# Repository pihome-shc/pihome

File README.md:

<p align="center">
    
<br/>
</p>

# PiHome - Smart Heating Control

PiHome – Smart Heating Control is home automation system or you can say central heating control systems that runs on credit card size single board computer Raspberry Pi. You can control your home heating from your smartphone, laptop or tablet, PiHome is a wireless boiler control which mean you don’t need to run cables from pihome controller to your boiler or to your heating zone valve or to any temperature sensors in any heating zone.PiHome is active heating control of your multi zoned heating, hot water including electrical immersion with unlimited schedules, boost and night climate suites your needs.

[Step by Step Instructions](http://www.pihome.eu/how-to-install/ "PiHome - Step by Step Instructions")

<p style="color:red;">Before we deep dive into this project something very important: PiHome comes with ABSOLUTELY NO WARRANTY, to the extent permitted by applicable law. DO NOT MAKE ANY CHANGES TO YOUR HEATING SYSTEM UNTIL UNLESS YOU KNOW WHAT YOU ARE DOING, contents provided here are for information and education purpose only, I take no responsibility for any loss or damage to you or your property.”</p3>

###If you want to download SD card image for Raspberry Pi please visit http://www.pihome.eu 

## Smart Heating Control – Features:
* Support Serial Gateway
* Support Ethernet and WiFi Gateway
* Unlimited schedule 
* Boiler and heating zone usage graphs
* Boost control for each Zone
* Override for each Zone
* Night climate
* Away

## Planned features
A real documentation (currently there's none, but the code is self explanatory and commented as well )

Follow Instructions on [PiHome](http://www.pihome.eu "PiHome - Smart Heating Control") if you have any question drop me comments and i will do my best to reply as soon as humanely possible. 

## Requirements
Basic knowledge of command line with following main components for pihome to function. 
* Apache Web Server
* PHP 7.x
* MySQL/MariaDB 

## How To Install 
sudo apt-get install git
sudo git clone https://github.com/pihome-shc/pihome "/var/www"
For more detailed instructiosn vist [PiHome](http://www.pihome.eu "PiHome - Smart Heating Control") website 

## Secial Thanks to

* [SB Admin 2 Template](http://startbootstrap.com/template-overviews/sb-admin-2 "SB Admin 2 Template ")
* [Pretty Checkbox](http://www.cssscript.com/pretty-checkbox-radio-inputs-bootstrap-awesome-bootstrap-checkbox-css "Pretty Checkbox ")
* [Font-Awesome](https://fortawesome.github.io/Font-Awesome "Font-Awesome")
* [Ionicons](http://ionicons.com "Ionicons ")
* [Box Shadow CSS](http://www.cssmatic.com/box-shadow "Box Shadow CSS")
* [AnimateCSS](https://daneden.github.io/animate.css "Animate.css ")
* [MySensors](https://www.mysensors.org "MySensors")
* [RaspberryPi Home Automation](http://pihome.harkemedia.de "RaspberryPi Home Automation")
* [All Others if forget them...](http://www.pihome.eu "All Others if forget them...")

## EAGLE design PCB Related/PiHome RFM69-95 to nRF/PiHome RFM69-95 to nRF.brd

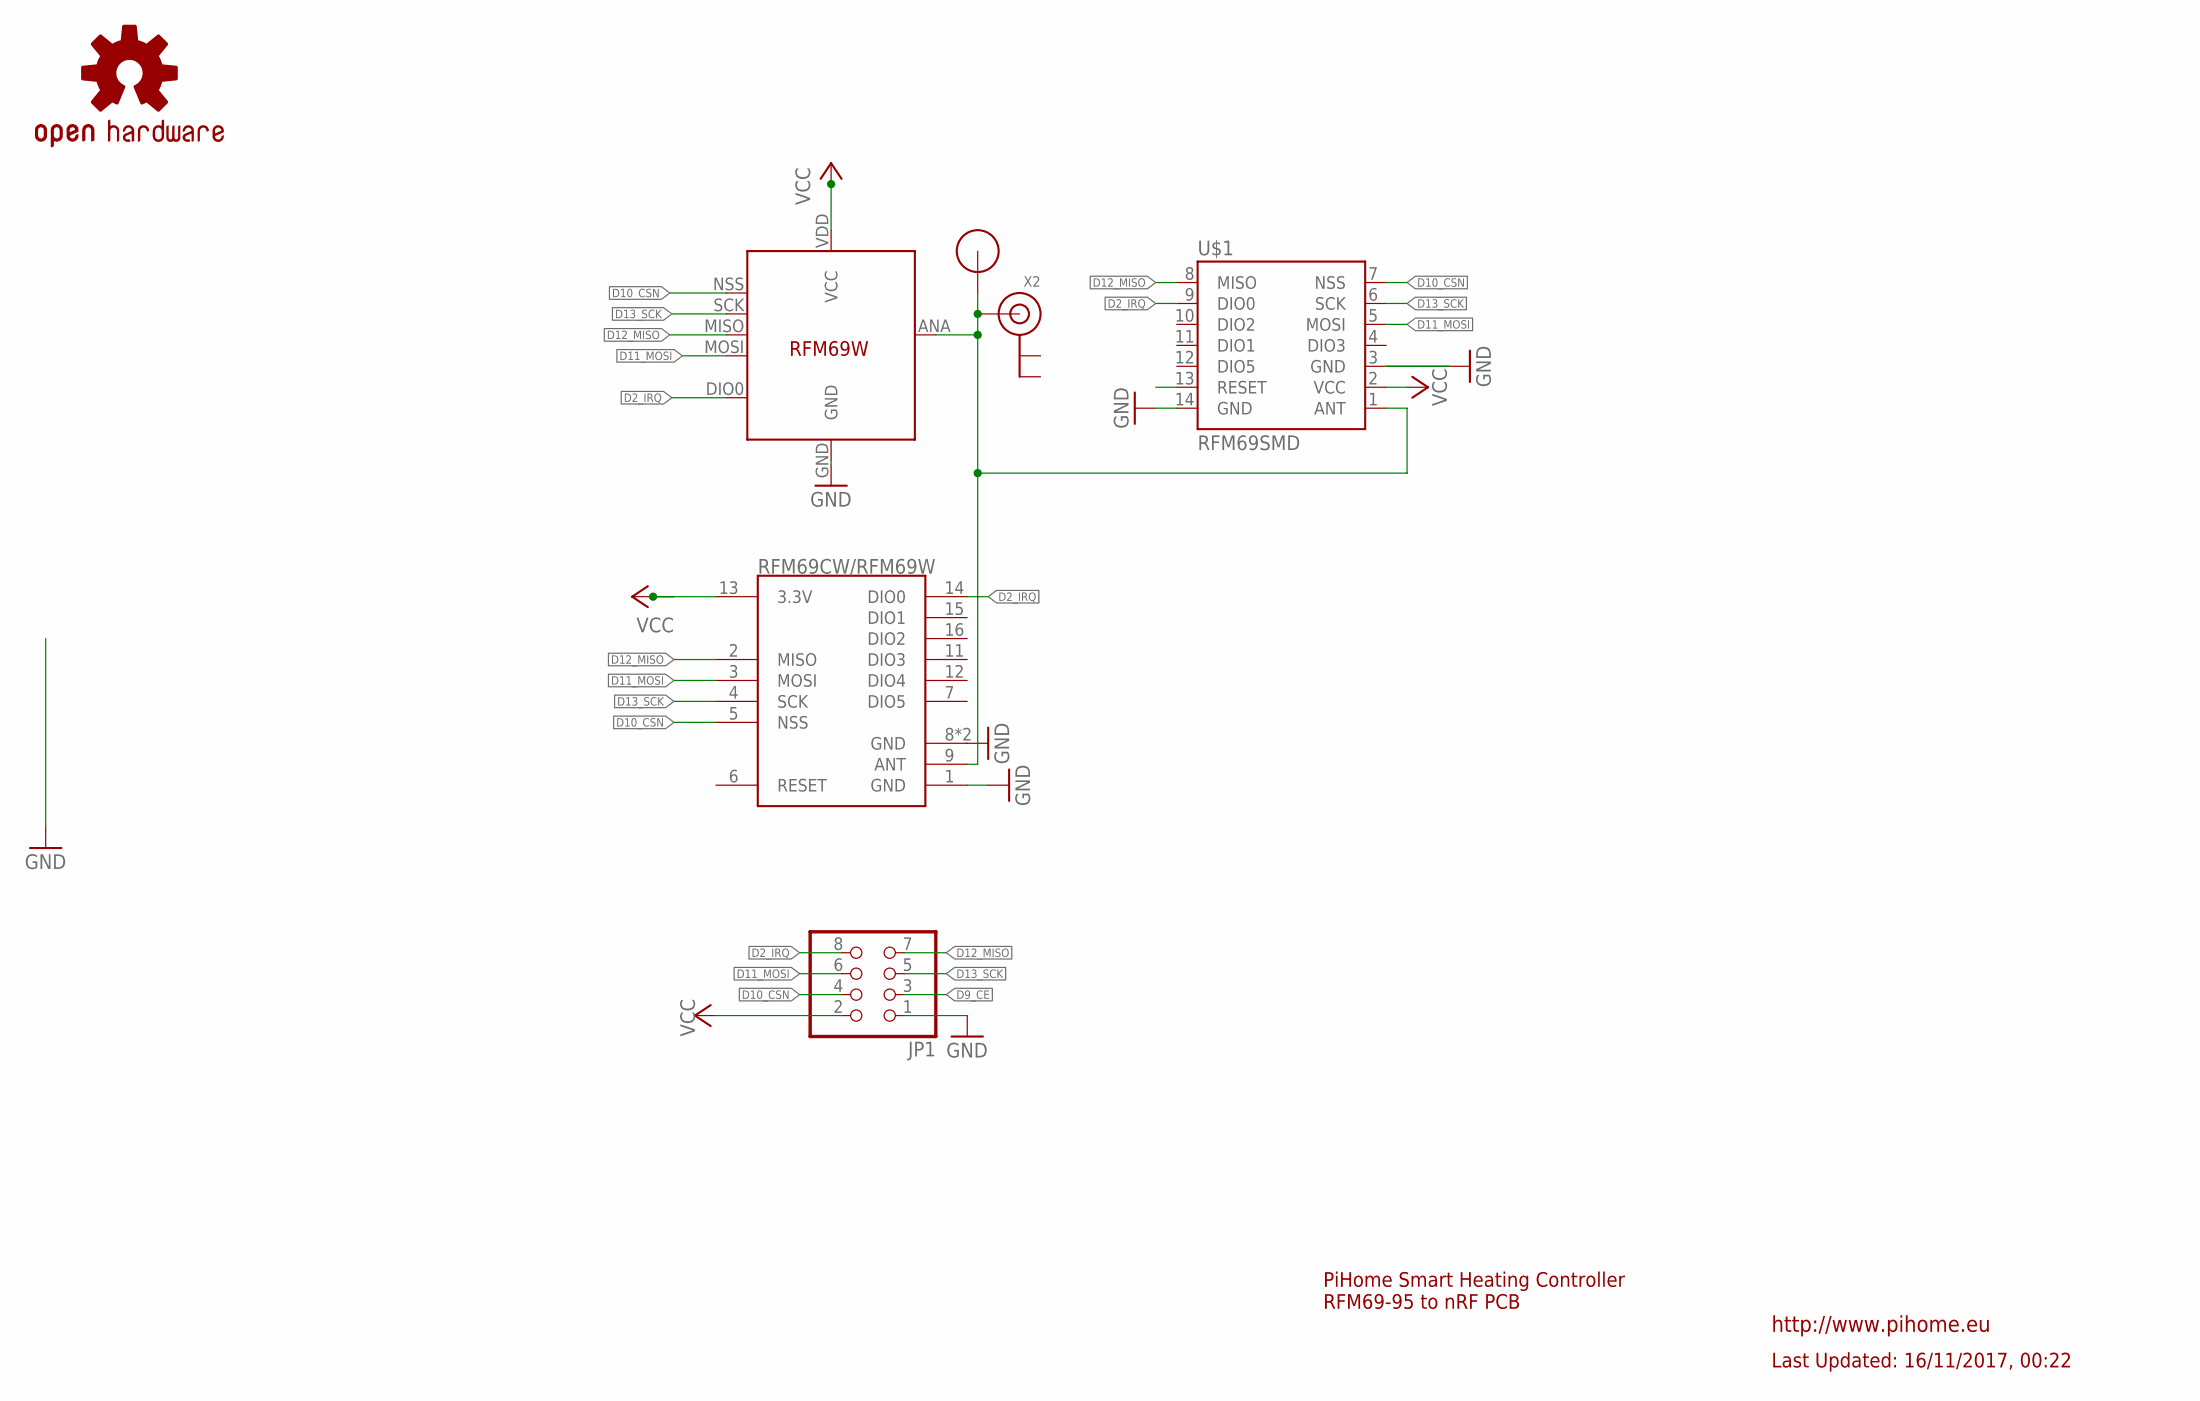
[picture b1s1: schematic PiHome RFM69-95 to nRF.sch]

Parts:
JP1: PINHD-2X4; 2X04
LOGO2: OSHW-LOGOS; OSHW-LOGO-S
RFM69CW/RFM69W: RFM69HCW; RFM69HCW-XXXS2
RFM69W-433MHZ: RFM69; RFM69W-MINPADS
U$1: RFM69SMD; RFM69
U$6: RFM12B_ANTENNA; RFM12B-ANTENNA
X2: ANTENNA_U.FL; U.FL

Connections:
D2_IRQ: JP1.8, RFM69CW/RFM69W.14 (DIO0), RFM69W-433MHZ.DIO0, U$1.9 (DIO0)
D9_CE: JP1.3
D10_CSN: JP1.4, RFM69CW/RFM69W.5 (NSS), RFM69W-433MHZ.NSS (SEL), U$1.7 (NSS)
D11_MOSI: JP1.6, RFM69CW/RFM69W.3 (MOSI), RFM69W-433MHZ.MOSI, U$1.5 (MOSI)
D12_MISO: JP1.7, RFM69CW/RFM69W.2 (MISO), RFM69W-433MHZ.MISO, U$1.8 (MISO)
D13_SCK: JP1.5, RFM69CW/RFM69W.4 (SCK), RFM69W-433MHZ.SCK, U$1.6 (SCK)
GND: JP1.1, RFM69CW/RFM69W.1 (GND), RFM69CW/RFM69W.8 (GND), RFM69CW/RFM69W.10 (GND), RFM69W-433MHZ.GND, U$1.3 (GND), U$1.14 (GND)
unnamed: RFM69CW/RFM69W.9 (ANT), RFM69W-433MHZ.ANA (ANT), U$1.1 (ANT), U$6.P$1, X2.3 (SIGNAL)
VCC: JP1.2, RFM69CW/RFM69W.13 (3.3V), RFM69W-433MHZ.VDD (VCC), U$1.2 (VCC)

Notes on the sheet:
PiHome Smart Heating Controller RFM69-95 to nRF PCB
Last Updated: 16/11/2017, 00:22
http://www.pihome.eu

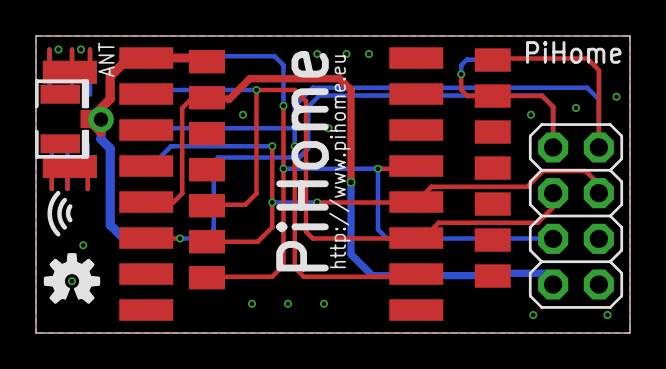
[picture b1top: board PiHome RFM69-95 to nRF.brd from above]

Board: 2 copper layers, 33.0 x 16.5 mm, 7 parts (1 on the bottom side), 8 nets.

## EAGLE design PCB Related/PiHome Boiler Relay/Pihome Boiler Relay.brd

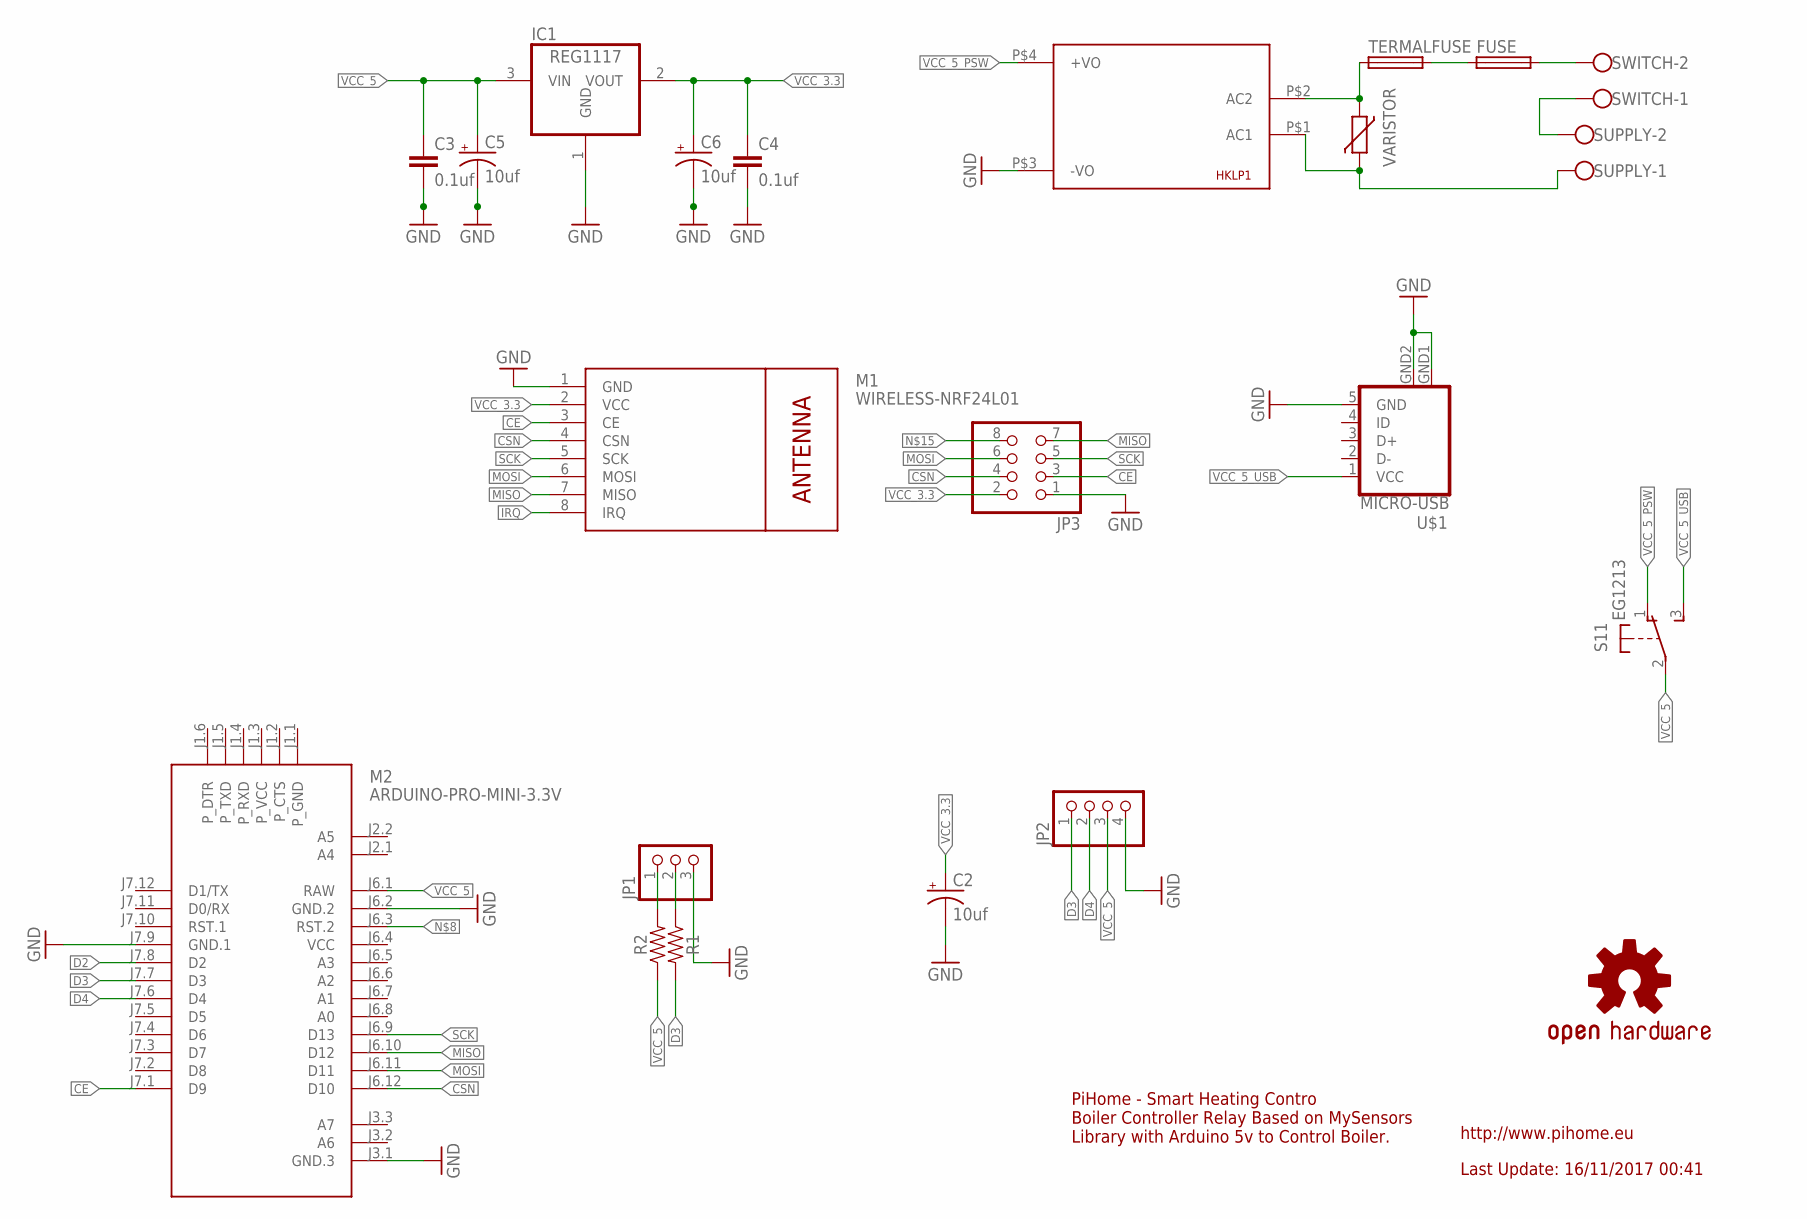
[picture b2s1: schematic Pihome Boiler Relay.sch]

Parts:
C2, C5, C6: 10uf; CPOL-RADIAL-10UF-25V-KIT
C3, C4: 0.1uf; CAP-PTH-SMALL-KIT
FUSE: TE5
HKLP1: HKLPM01
IC1: REG1117; SOT223
JP1: PINHD-1X3; 1X03
JP2: PINHD-1X4; 1X04
JP3: PINHD-2X4; 2X04
LOGO1: OSHW-LOGOL; OSHW-LOGO-L
M1: WIRELESS-NRF24L01
M2: ARDUINO-PRO-MINI-3.3V; ARDUINO-PRO-MINI
R1, R2: AXIAL-0.3
S1: EG1213
SUPPLY: W237-102
SWITCH: W237-102
TERMALFUSE: TE5
U$1: MICRO-USB
VARISTOR: VARISTOR-7,5; R-7,5

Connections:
CE: JP3.3, M1.3 (CE), M2.J7.1 (D9)
CSN: JP3.4, M1.4 (CSN), M2.J6.12 (D10)
D2: M2.J7.8 (D2)
D3: JP2.1, M2.J7.7 (D3), R1.P$2 (2)
D4: JP2.2, M2.J7.6 (D4)
GND: C2.2 (-), HKLP1.P$3 (-VO), JP1.3, JP2.4, JP3.1, M1.1 (GND), M2.J3.1 (GND.3), M2.J6.2 (GND.2), M2.J7.9 (GND.1), U$1.5 (GND), U$1.GND1 (GND), U$1.GND2 (GND)
GND-: C3.2, C4.2, C5.2 (-), C6.2 (-), IC1.1 (GND)
IRQ: M1.8 (IRQ)
MISO: JP3.7, M1.7 (MISO), M2.J6.10 (D12)
MOSI: JP3.6, M1.6 (MOSI), M2.J6.11 (D11)
unnamed: SUPPLY.2, SWITCH.1
unnamed: FUSE.1, TERMALFUSE.2
unnamed: HKLP1.P$2 (AC2), TERMALFUSE.1, VARISTOR.1
unnamed: HKLP1.P$1 (AC1), SUPPLY.1, VARISTOR.2
unnamed: JP1.2, R1.P$1 (1)
unnamed: JP1.1, R2.P$2 (2)
unnamed: FUSE.2, SWITCH.2
SCK: JP3.5, M1.5 (SCK), M2.J6.9 (D13)
VCC: M2.J6.4 (VCC)
VCC_3.3: C2.1 (+), C4.1, C6.1 (+), IC1.2 (VOUT), JP3.2, M1.2 (VCC)
VCC_5: C3.1, C5.1 (+), IC1.3 (VIN), JP2.3, M2.J6.1 (RAW), R2.P$1 (1), S1.2
VCC_5_PSW: HKLP1.P$4 (+VO), S1.1 (O)
VCC_5_USB: S1.3 (S), U$1.1 (VCC)

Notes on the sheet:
Last Update: 16/11/2017 00:41
http://www.pihome.eu
PiHome - Smart Heating Contro Boiler Controller Relay Based on MySensors Library with Arduino 5v to Control Boiler.

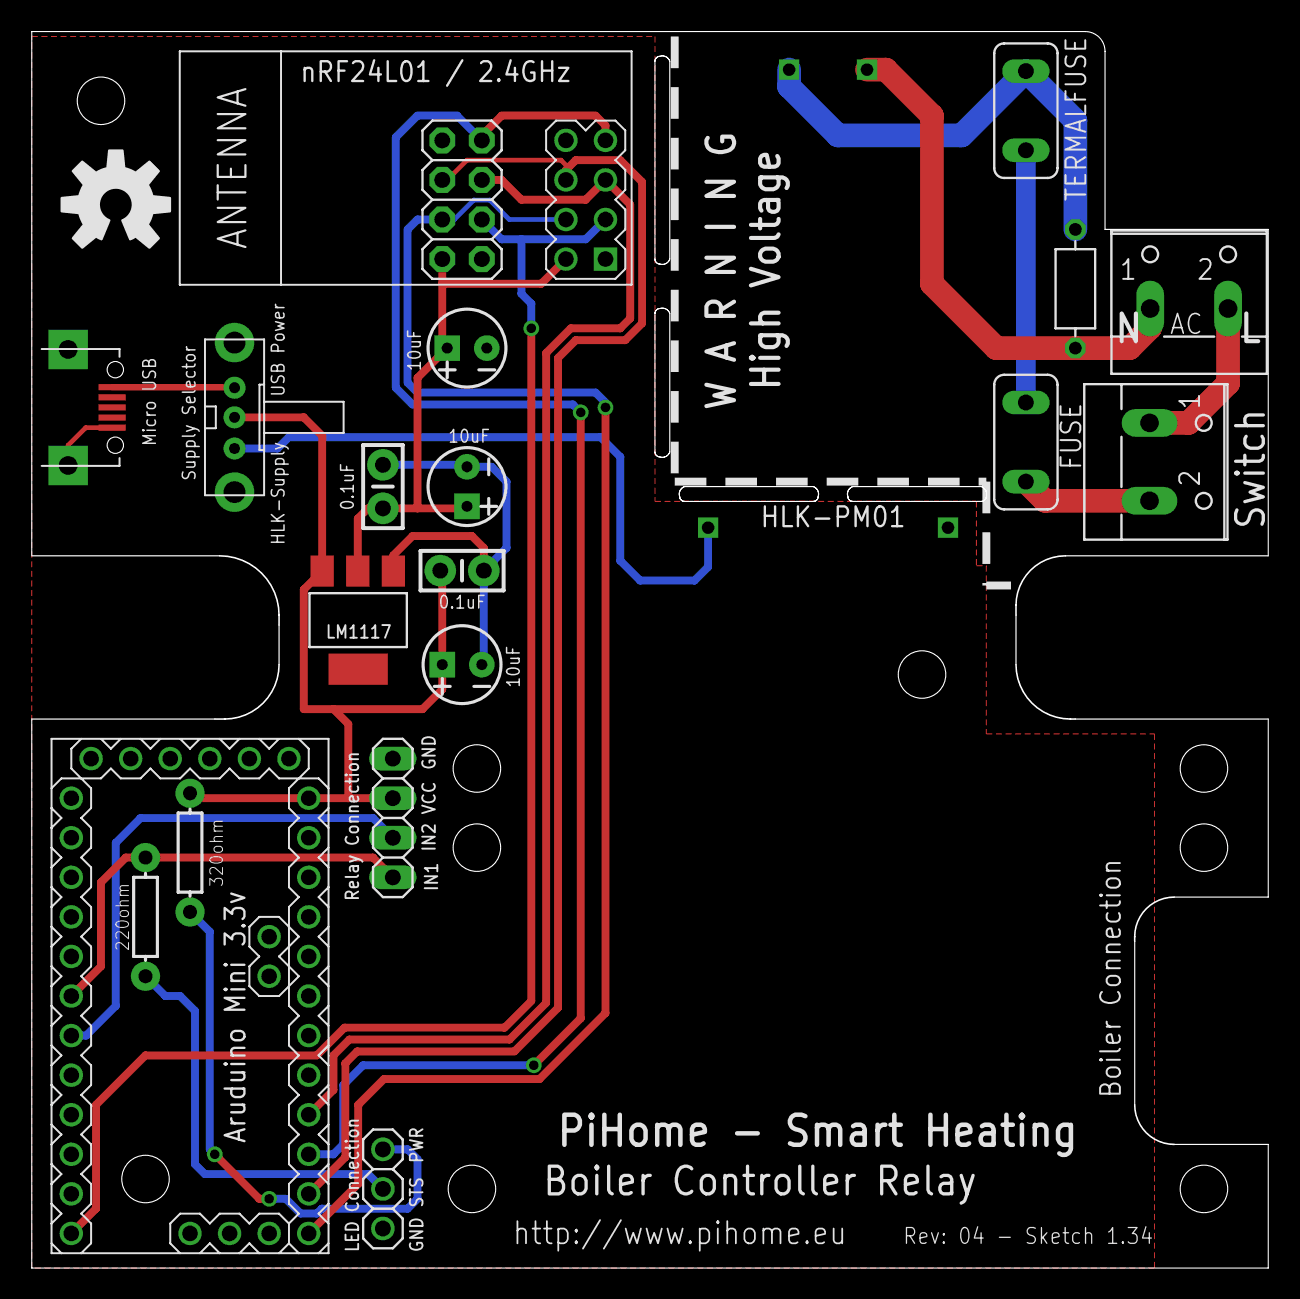
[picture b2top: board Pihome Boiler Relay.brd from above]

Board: 2 copper layers, 79.4 x 79.4 mm, 22 parts (0 on the bottom side), 20 nets.

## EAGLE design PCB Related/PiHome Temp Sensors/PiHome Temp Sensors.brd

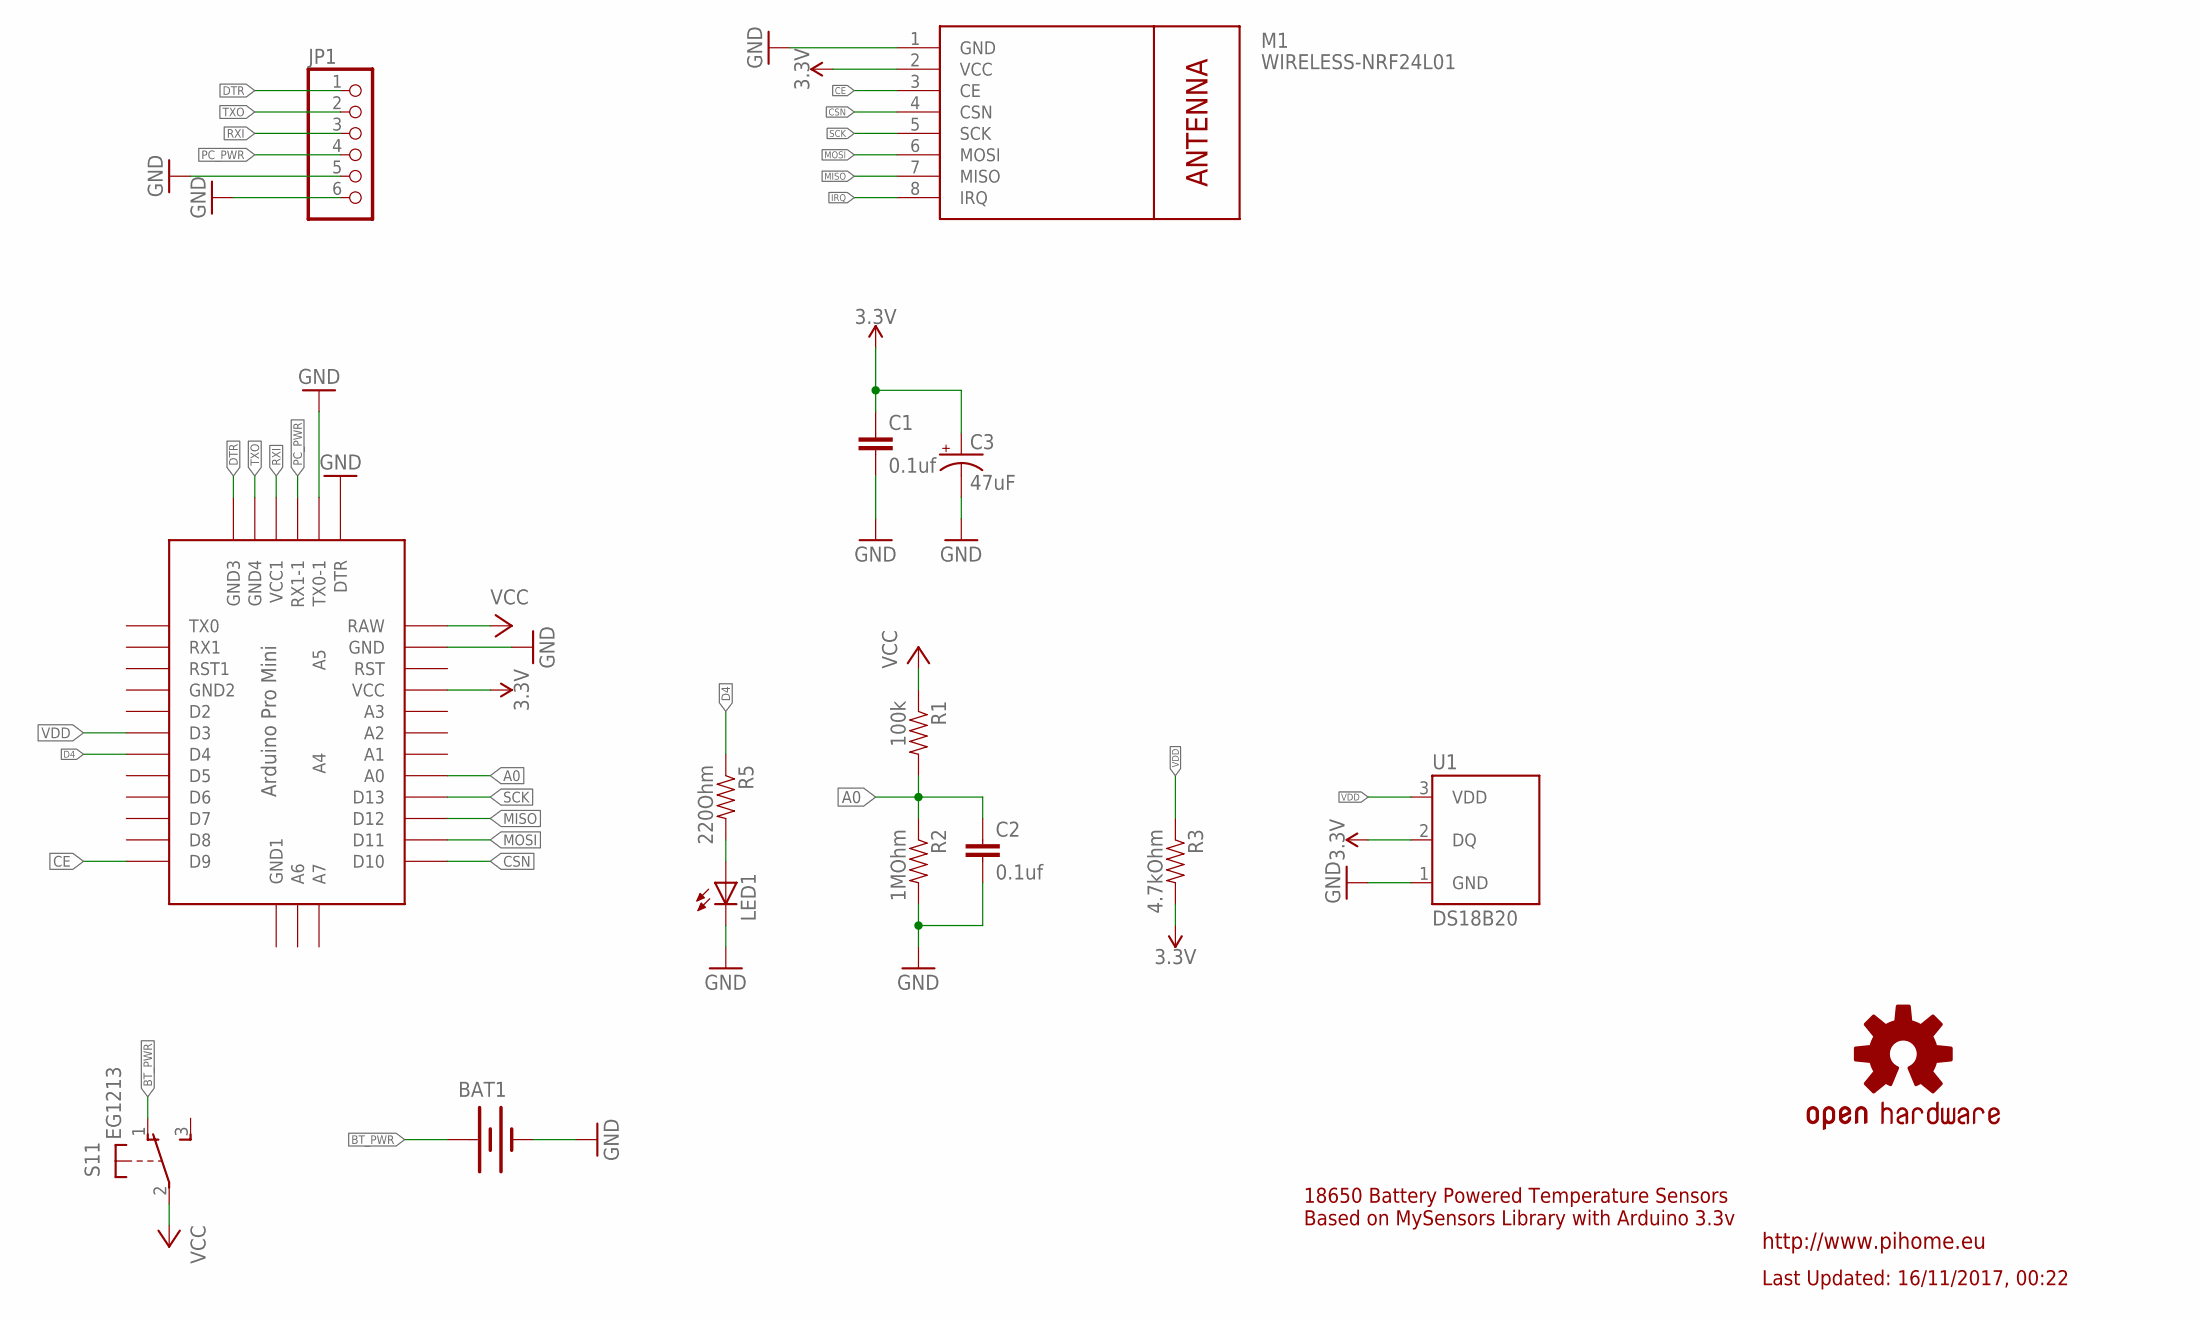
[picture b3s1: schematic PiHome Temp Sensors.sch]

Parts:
BAT1: BATTERY18650; BATTERY_18650-HOLDER
C1, C2: 0.1uf; CAP-PTH-SMALL-KIT
C3: 47uF; CPOL-RADIAL-10UF-25V-KIT
JP1: PINHD-1X6; 1X06
LED1: LED3MM
LOGO1: OSHW-LOGOL; OSHW-LOGO-L
M1: WIRELESS-NRF24L01
R1: 100k; AXIAL-0.3
R2: 1MOhm; AXIAL-0.3
R3: 4.7kOhm; AXIAL-0.3
R5: 220Ohm; AXIAL-0.3
S1: EG1213
U1: DS18B20; TO-92-AMMO
U$1: ABK-PRO-MINI

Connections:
3.3V: C1.1, C3.1 (+), M1.2 (VCC), R3.P$2 (2), U1.2 (DQ), U$1.VCC
A0: C2.1, R1.P$2 (2), R2.P$1 (1), U$1.A0
BT_PWR: BAT1.PWR@1 (+), S1.1 (O)
CE: M1.3 (CE), U$1.D9
CSN: M1.4 (CSN), U$1.D10
D4: R5.P$1 (1), U$1.D4
DTR: JP1.1, U$1.GND2 (GND3)
GND: BAT1.GND@1 (-), C1.2, C2.2, C3.2 (-), JP1.5, JP1.6, LED1.K (C), M1.1 (GND), R2.P$2 (2), U1.1 (GND), U$1.DTR, U$1.GND, U$1.TX0-1
IRQ: M1.8 (IRQ)
MISO: M1.7 (MISO), U$1.D12
MOSI: M1.6 (MOSI), U$1.D11
unnamed: LED1.A, R5.P$2 (2)
PC_PWR: JP1.4, U$1.RX1-1
RXI: JP1.3, U$1.VCC1
SCK: M1.5 (SCK), U$1.D13
TXO: JP1.2, U$1.GND3 (GND4)
VCC: R1.P$1 (1), S1.2, U$1.RAW
VDD: R3.P$1 (1), U1.3 (VDD), U$1.D3

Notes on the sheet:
18650 Battery Powered Temperature Sensors Based on MySensors Library with Arduino 3.3v
Last Updated: 16/11/2017, 00:22
http://www.pihome.eu

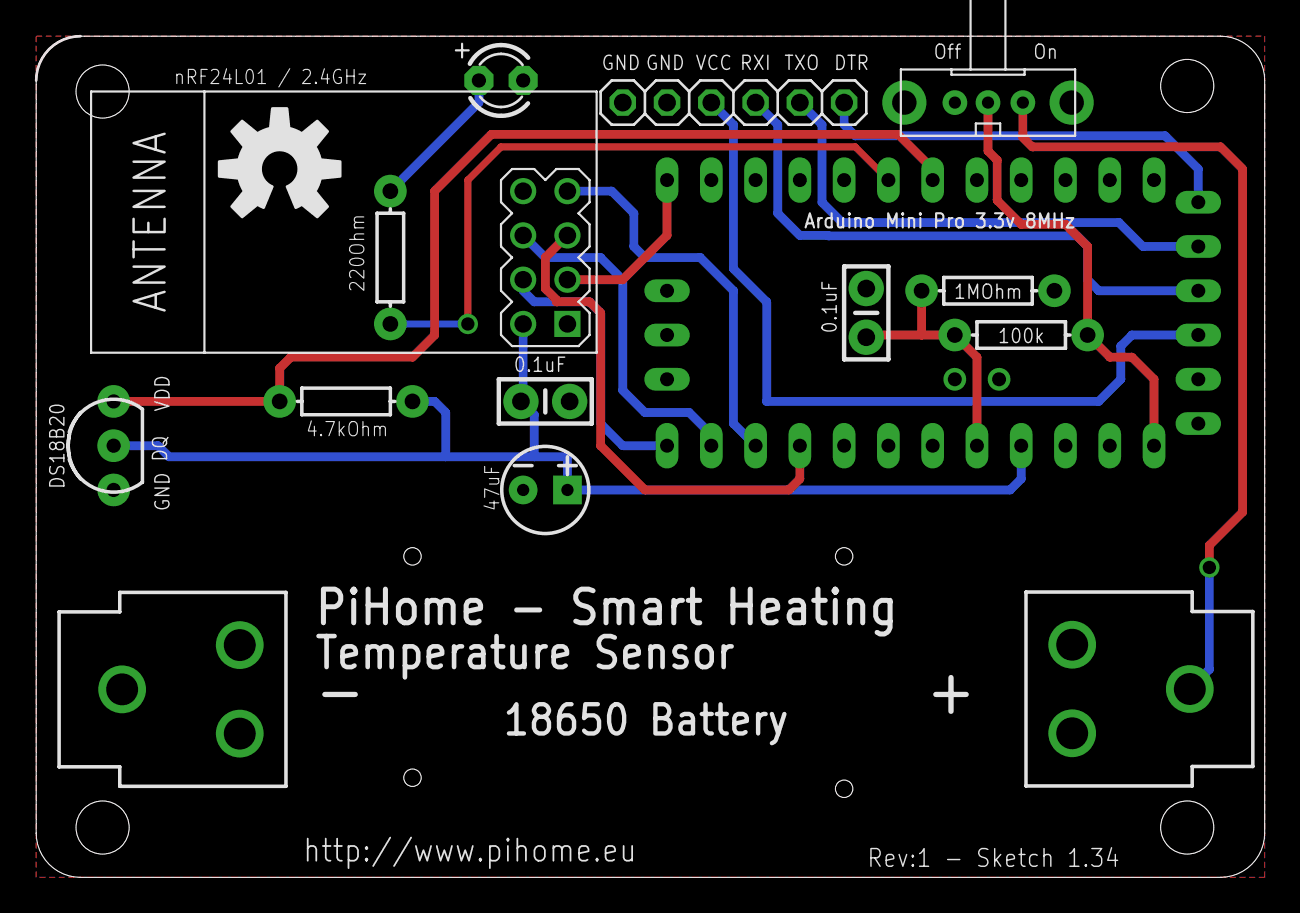
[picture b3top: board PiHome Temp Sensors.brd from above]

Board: 2 copper layers, 70.5 x 48.3 mm, 15 parts (0 on the bottom side), 17 nets.

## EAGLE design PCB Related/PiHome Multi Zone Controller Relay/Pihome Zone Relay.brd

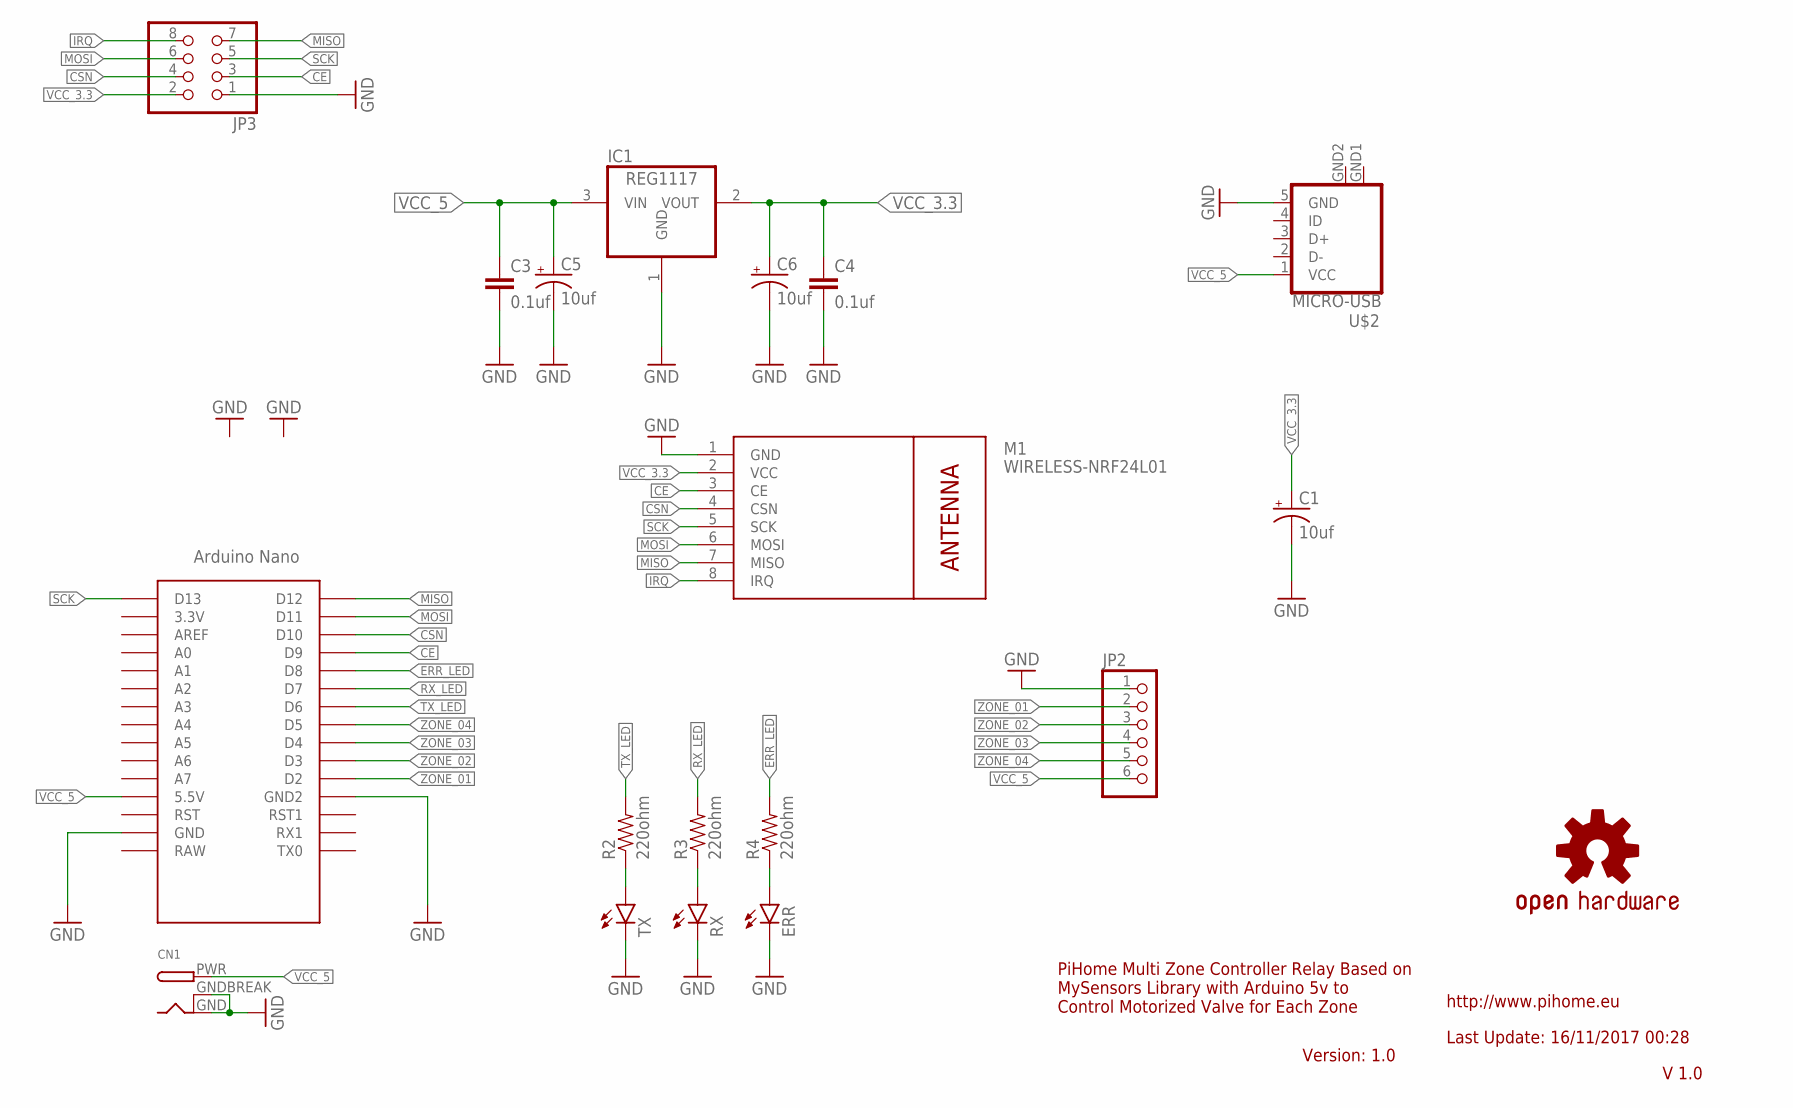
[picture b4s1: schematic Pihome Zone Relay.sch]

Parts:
C1, C5, C6: 10uf; CPOL-RADIAL-10UF-25V-KIT
C3, C4: 0.1uf; CAP-PTH-SMALL-KIT
CN1: DCBARRELPTH; DCJACK_2MM_PTH
ERR: LED3MM
IC1: REG1117; SOT223
JP2: PINHD-1X6; 1X06
JP3: PINHD-2X4; 2X04
LOGO4: OSHW-LOGOM; OSHW-LOGO-M
M1: WIRELESS-NRF24L01
R2, R3, R4: 220ohm; AXIAL-0.3
RX: LED3MM
TX: LED3MM
U$1: NANO
U$2: MICRO-USB

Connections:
CE: JP3.3, M1.3 (CE), U$1.D9
CSN: JP3.4, M1.4 (CSN), U$1.D10
ERR_LED: R4.P$2 (2), U$1.D8
GND: C1.2 (-), C3.2, C4.2, C5.2 (-), C6.2 (-), CN1.GND, CN1.GNDBREAK, ERR.K (C), IC1.1 (GND), JP2.1, JP3.1, M1.1 (GND), RX.K (C), TX.K (C), U$1.GND, U$1.GND1 (GND2), U$2.5 (GND), U$2.GND1 (GND), U$2.GND2 (GND)
IRQ: JP3.8, M1.8 (IRQ)
MISO: JP3.7, M1.7 (MISO), U$1.D12
MOSI: JP3.6, M1.6 (MOSI), U$1.D11
unnamed: R2.P$1 (1), TX.A
unnamed: R3.P$1 (1), RX.A
unnamed: ERR.A, R4.P$1 (1)
RX_LED: R3.P$2 (2), U$1.D7
SCK: JP3.5, M1.5 (SCK), U$1.D13
TX_LED: R2.P$2 (2), U$1.D6
VCC_3.3: C1.1 (+), C4.1, C6.1 (+), IC1.2 (VOUT), JP3.2, M1.2 (VCC)
VCC_5: C3.1, C5.1 (+), CN1.PWR, IC1.3 (VIN), JP2.6, U$1.5V (5.5V), U$2.1 (VCC)
ZONE_01: JP2.2, U$1.D2
ZONE_02: JP2.3, U$1.D3
ZONE_03: JP2.4, U$1.D4
ZONE_04: JP2.5, U$1.D5

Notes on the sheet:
http://www.pihome.eu
Last Update: 16/11/2017 00:28
PiHome Multi Zone Controller Relay Based on MySensors Library with Arduino 5v to Control Motorized Valve for Each Zone
Version: 1.0
V 1.0

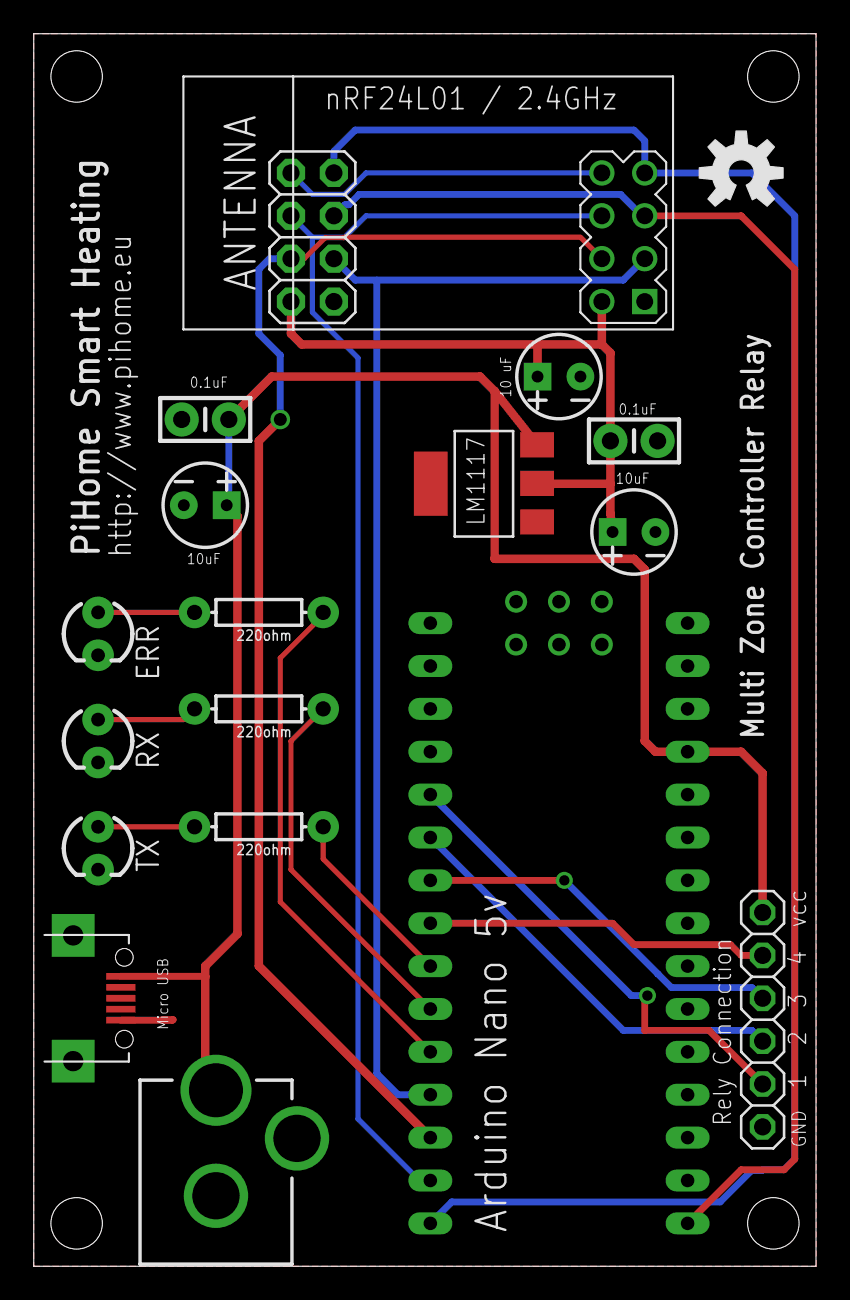
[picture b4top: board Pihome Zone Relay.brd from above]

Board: 2 copper layers, 46.3 x 73.0 mm, 19 parts (0 on the bottom side), 19 nets.

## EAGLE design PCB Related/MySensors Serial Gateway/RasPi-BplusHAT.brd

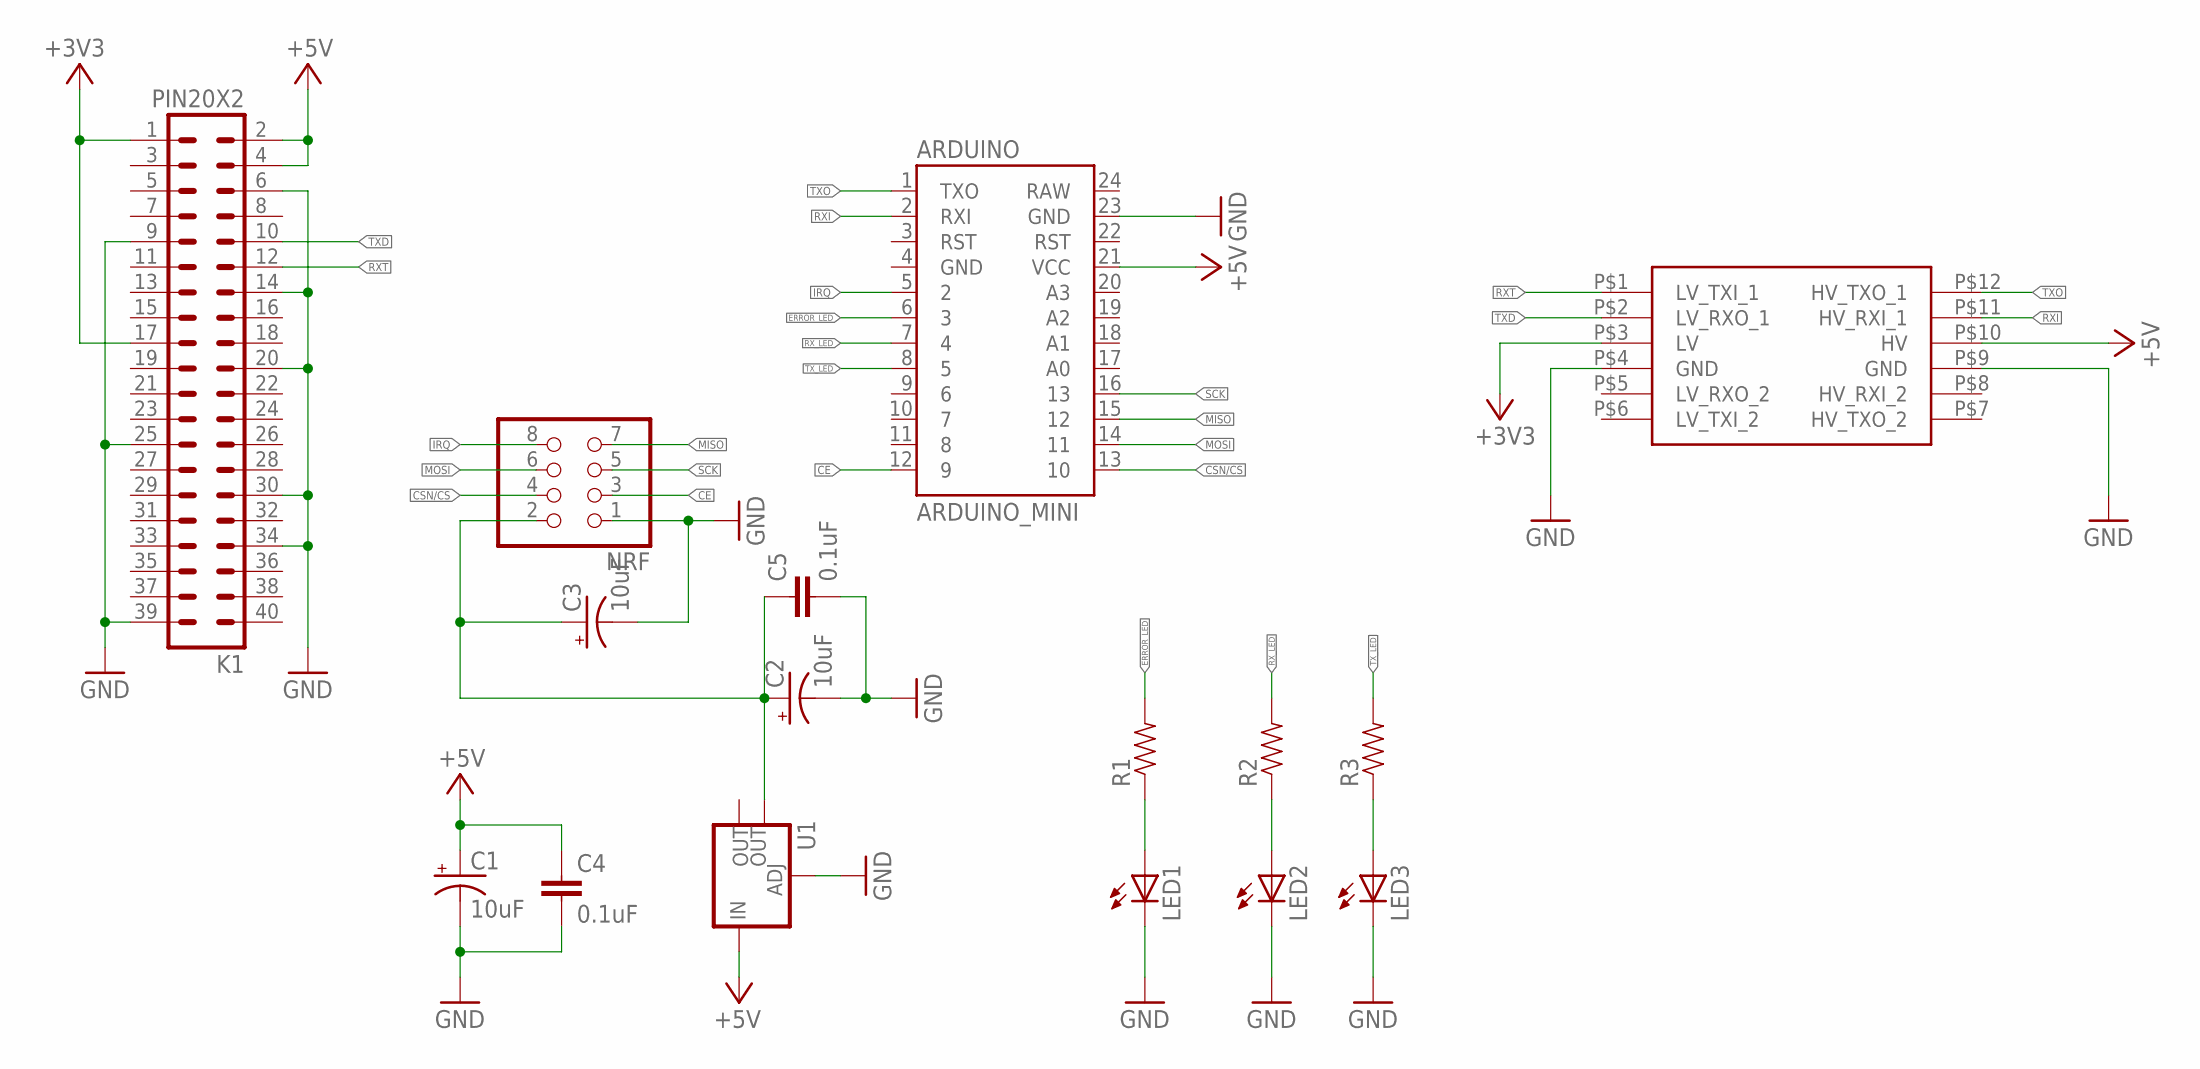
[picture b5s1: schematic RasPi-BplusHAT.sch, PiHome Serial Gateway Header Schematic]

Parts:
ARDUINO: ARDUINO_MINI
C1, C2, C3: 10uF; CPOL-RADIAL-10UF-25V
C4, C5: 0.1uF; CAP-PTH-SMALL
K1: PIN20X2; PIN_20X2
LED1, LED2, LED3: LED3MM
NRF: PINHD-2X4; 2X04
R1, R2, R3: RESISTORPTH-1/4W; AXIAL-0.4
U1: V_REG_LM1117SOT223; SOT223
U$2: LOGIC_LEVEL_CONVERTER

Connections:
+3V3: K1.1, K1.17, U$2.P$3 (LV)
+5V: ARDUINO.21 (VCC), C1.1 (+), C4.1, K1.2, K1.4, U1.3 (IN), U$2.P$10 (HV)
CE: ARDUINO.12 (9), NRF.3
CSN/CS: ARDUINO.13 (10), NRF.4
ERROR_LED: ARDUINO.6 (3), R1.P$2 (2)
GND: ARDUINO.23 (GND), C1.2 (-), C2.2 (-), C3.2 (-), C4.2, C5.2, K1.6, K1.9, K1.14, K1.20, K1.25, K1.30, K1.34, K1.39, LED1.K (C), LED2.K (C), LED3.K (C), NRF.1, U1.1 (ADJ), U$2.P$4 (GND), U$2.P$9 (GND)
IRQ: ARDUINO.5 (2), NRF.8
MISO: ARDUINO.15 (12), NRF.7
MOSI: ARDUINO.14 (11), NRF.6
unnamed: C2.1 (+), C3.1 (+), C5.1, NRF.2, U1.4 (OUT)
unnamed: LED1.A, R1.P$1 (1)
unnamed: LED2.A, R2.P$1 (1)
unnamed: LED3.A, R3.P$1 (1)
RXI: ARDUINO.2 (RXI), U$2.P$11 (HV_RXI_1)
RXT: K1.12, U$2.P$1 (LV_TXI_1)
RX_LED: ARDUINO.7 (4), R2.P$2 (2)
SCK: ARDUINO.16 (13), NRF.5
TXD: K1.10, U$2.P$2 (LV_RXO_1)
TXO: ARDUINO.1 (TXO), U$2.P$12 (HV_TXO_1)
TX_LED: ARDUINO.8 (5), R3.P$2 (2)

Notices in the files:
parts and their libraries:
SparkFun-Boards: Licensing: Creative Commons ShareAlike 4.0 International - https://creativecommons.org/licenses/by-sa/4.0
diy-modules: Released under the Creative Commons Attribution 4.0 International License: http://creativecommons.org/licenses/by/4.0
